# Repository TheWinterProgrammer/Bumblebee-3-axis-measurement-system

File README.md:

# Bumblebee 3-Axis Measurement System

## Overview

The **Bumblebee 3-Axis Measurement System** is a versatile, open-source, cubic positioning robot adapted for low-field MRI research. This project builds upon the design of the original [COSI Measure Robot](https://www.opensourceimaging.org/project/cosi-measure/), enhancing its mechanical and electronic capabilities. The system was redesigned during the 2023-2024 academic year as part of several bachelor theses at our institute.

### Key Features
- **Adapted Mechanical Design**  
  The robot is designed for:
  - A larger measurement volume.
  - Improved efficiency relative to the robot's size.

- **Simplified Electronics**  
  Replacing the BeagleBone Black and embedded Linux system, the new design features:
  - An **Arduino MEGA** as the central microcontroller for motor control, limit switch evaluation, and serial communication.
  - A **Python-based host PC script** to:
    - Control mapping.
    - Communicate positions to the robot.
    - Interface with the Hall sensor.

- **Sensor Integration**  
  The current setup uses the **F.W. BELL Series 9900 Hall sensor** with the ZOA99-3208 3D Hall probe. The Python script processes data from this sensor via serial communication. However, the system can accommodate other sensors as needed.

---

## Publication

This work was presented and published as a conference paper:  
**Samlow J, Maltsev S [TheWinterProgrammer](https://github.com/TheWinterProgrammer), Buckenmaier K, Scheffler K, Povolni P [ppolGTMonster](https://github.com/ppolGTMonster) (2024). Easy Rebuildable Cubic 3-Axis Positioning Robot Based on Open-Source Hardware: Validated via Camera-Based Motion Tracking and Initial Application in Magnetic Low Field Mapping.** *DACH-ISMRM 2024 Program & Proceedings, Tübingen, Germany*, pp. 1–2.

---

## Getting Started

There a tree major parts:

### System Components
1. **Hardware** [here](Hardware)
   - Rebuilt mechanical design for larger volume mapping.
   - Compact yet efficient cubic robot frame.

2. **Electronics** 
   - Arduino MEGA for robot control and interfacing [here](Software/Arduino/).
   - Support for various sensors through serial communication.

3. **Software** [here](Software/PythonGUI/)
   - Python script to manage mapping and communication.

### Usage
1. Set up the Arduino MEGA and connect the motors, limit switches, and Hall sensor.
2. Run the Python script on the host PC for:
   - Position control of the robot.
   - Real-time data collection from the Hall sensor.

---
## Author
   - Judith Samlov ([E-Mail](judith.samlov@tuebingen.mpg.de)), (Hardware and Software) 
   - Pavel Povolni ([E-Mail](pavel.povolni@tuebingen.mpg.de), [Github](https://github.com/ppolGTMonster)), (Hardware and Software)
   - Sergej Maltsev ([E-Mail](sergej.maltsev@tuebingen.mpg.de), [Github](https://github.com/TheWinterProgrammer)), (Software Python GUI)

### Contact
For further inquiries or contributions, feel free to reach out through the repository.

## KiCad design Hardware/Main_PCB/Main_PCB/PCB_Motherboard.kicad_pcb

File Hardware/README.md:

# Hardware

## Assembly Robot

The assembly of the robot, including all CAD design files and instructions, is thoroughly described and documented in the following resources:  
- [COSI Measure Project Page](https://www.opensourceimaging.org/project/cosi-measure/)  
- [COSI Measure GitHub Repository](https://github.com/opensourceimaging/cosi-measure/tree/master/Mechanical%20System)  

We recommend referring to these resources for detailed instructions. The hardware components for the drive and ordering details are also described there.

### Key Components for 3D Drive
We used the following parts for the 3D drive. These may be relevant if adapting the PCB, though similar drives should also work:

- **Motor**: NEMA23 60HS88, 3 pieces (no longer available)  
  Alternative: [HYBRID NEMA-23 Stepper Motor](https://www.reichelt.de/hybridschrittmotor-nema-23-1-8-4-2-a-2-52-v-act-23hs9440-26-p316758.html?&trstct=pos_6&nbc=1)  
- **Motor Driver**: ACT DM542, 3 pieces  
  Link: [Stepper Motor Driver ACT DM542](https://www.reichelt.de/schrittmotortreiber-fuer-nema-23-18-50-v-act-dm542-p237924.html?&trstct=pos_1&nbc=1)  
- **Limit Switch**: LJ12A3-4-Z/BX DC6-36V, 3 pieces  
  Link: [Inductive Sensor](https://www.roboter-bausatz.de/p/induktiver-sensor-lj12a3-4-z-bx-dc6-36v?number=RBS11420)  
- **Power Source**: 36V, 9.75A (350W)  
  Link: [36V Power Supply](https://www.reichelt.de/schaltnetzteil-geschlossen-351-w-36-v-9-75-a-mw-uhp-350-36-p256082.html?&trstct=pol_6&nbc=1)  

---

## Assembly PCB

### General

For this version of COSI Measure, we used an **Arduino Mega** as the central microcontroller (µC).  

While assembling, some errors in the V1.0 PCB design were identified and corrected in version V2.0, which is made available here.  

This design uses a two-part concept:  
1. **Main PCB**  
2. **Optional Remote Control**  
   - The remote control can manually adjust the Hall sensor's position. Although the remote control functionality was disabled in this setup, the buttons and encoders remain available in the hardware. Manual control has been replaced by Python-based software control.

If needed, you can design your own remote control and connect it via the 26-pin SubD connector.

### Implemented Functions

- Control of 3 stepper motors via PWM signals.  
- Safety circuit with emergency stop to disconnect motor drivers' power supply.  
- I2C output, e.g., for display integration.  
- Serial communication (USB) with the host PC.  
- Other analog inputs/outputs are available and can be used e.g. for additional sensors.

### PCB Design
- Designed using **KiCad 8** (no additional packages required).  
- Comments in the schematic provide explanatory details.  
- Uses large SMD components (e.g., SMD1206 for resistors and capacitors) for easy soldering.  
- Two-layer PCB design to reduce manufacturing costs.  
- A bill of materials (BoM) is included in the accompanying Excel sheet.  

#### Note
The PCB size can be reduced by modifying component footprints and minimizing unused connectors.

### Assembly PCB
- Large component sizes simplify soldering.  
- Arduino Mega connects via pin headers for easy replacement.  
- A cutout in the PCB allows visibility of the Arduino's built-in LED when mounted.  

### Wiring Inside the Case
The PCB, power supply, and motor drivers are all housed in a single case. Wiring is straightforward with labeled connectors on the PCB. **Phoenix 3.81mm PCB connectors** were used to facilitate cable attachment.  

#### ⚠️ Important Safety Note:
<span style="color: red;">- The power supply operates at 230V AC, which is **extremely dangerous**.</span>  
<span style="color: red;">- Electrical connections between the power input and power supply are **not documented here**.</span>  
<span style="color: red;">- **Only a qualified electrician** should handle this part. Ensure the case is grounded and use an FI-protected socket.</span>

---

## Assembly Case for Electronics

### Case Design
The case is a standard **19-inch, 2 height units** enclosure. The side profiles, front and back panels, and top and bottom panels were milled using a mechanical workshop.  

For best results, the front and back panels should be milled. Alternatively, mounting holes can be created manually. Accuracy is essential for mounting the DSub connector.  

Cooling: Two 12V fans were installed but found unnecessary during operation. Drivers were mounted on the base plate with cooling fins extending outward for heat dissipation. However, this may not be required.

### CAD Files
The case design was created using **Autodesk Inventor 2022**.  
- Files are exported as STEP files for compatibility with other CAD programs.  
- Side profiles are customizable, depending on the electronics installed.  

### Front Connections
All parts for the front panel are listed in the BoM.  
- **USB**: For Arduino Mega-PC serial communication.  
- **Limit Switches**: 25-pin Sub-D (male) for connecting up to 6 limit switches.  
- **Remote Control**: 26-pin Sub-D (female).  
- **Motor Connections**: 4-pin DIN connectors (male) for X, Y, and Z-axis motors.  
- **Power LED**: Indicates power supply status.  
- **Emergency Stop**: Cuts power to motor drivers via relay.  

### Back Connections
- **230V IEC Plug**: Includes an on/off switch and main fuse (1.75A, slow-blow).  

### Wiring
Wiring is simplified by labeled PCB connectors and depends on the components installed. For questions, please contact us.

---

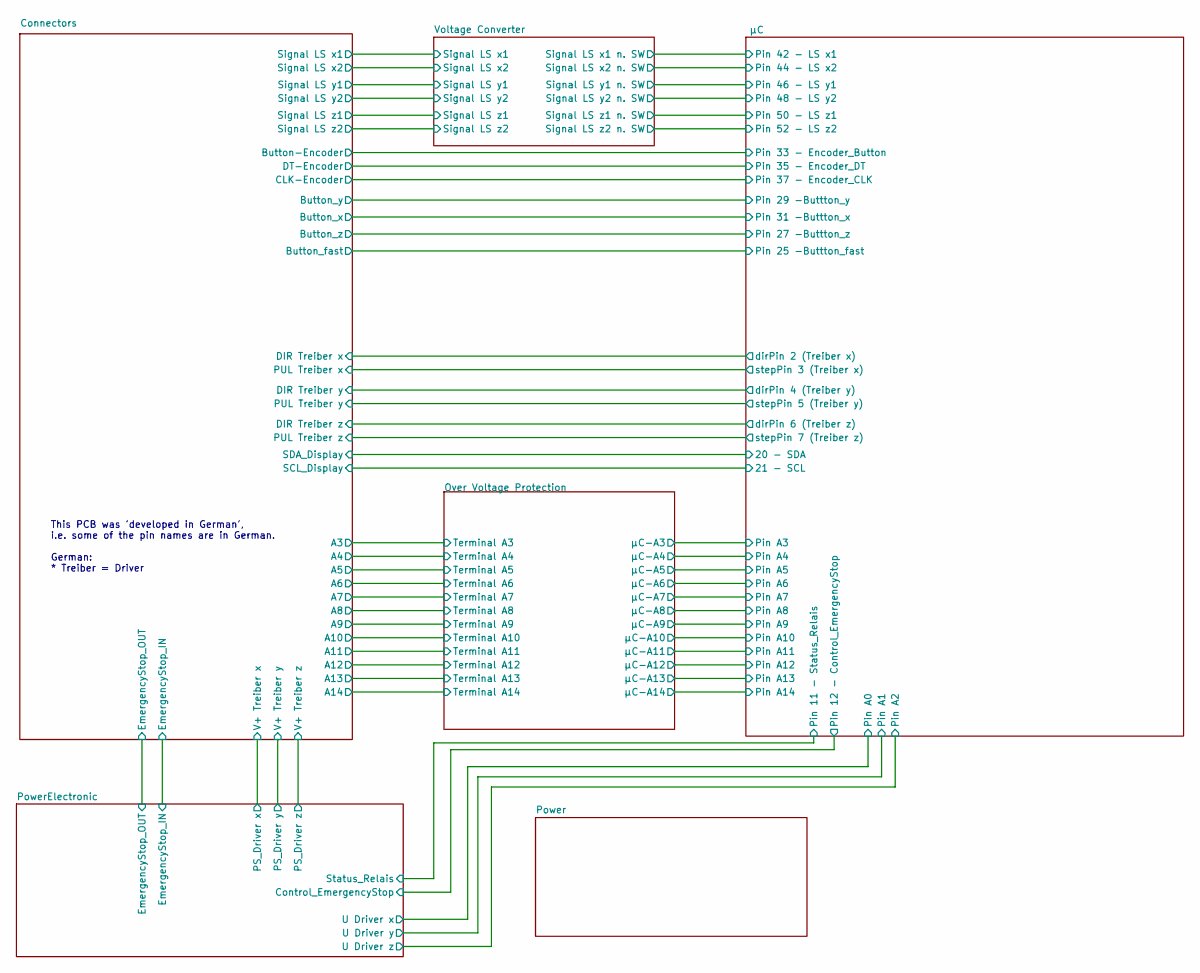
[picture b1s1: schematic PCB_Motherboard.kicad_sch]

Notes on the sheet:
This PCB was 'developed in German', i.e. some of the pin names are in German. German: * Treiber = Driver

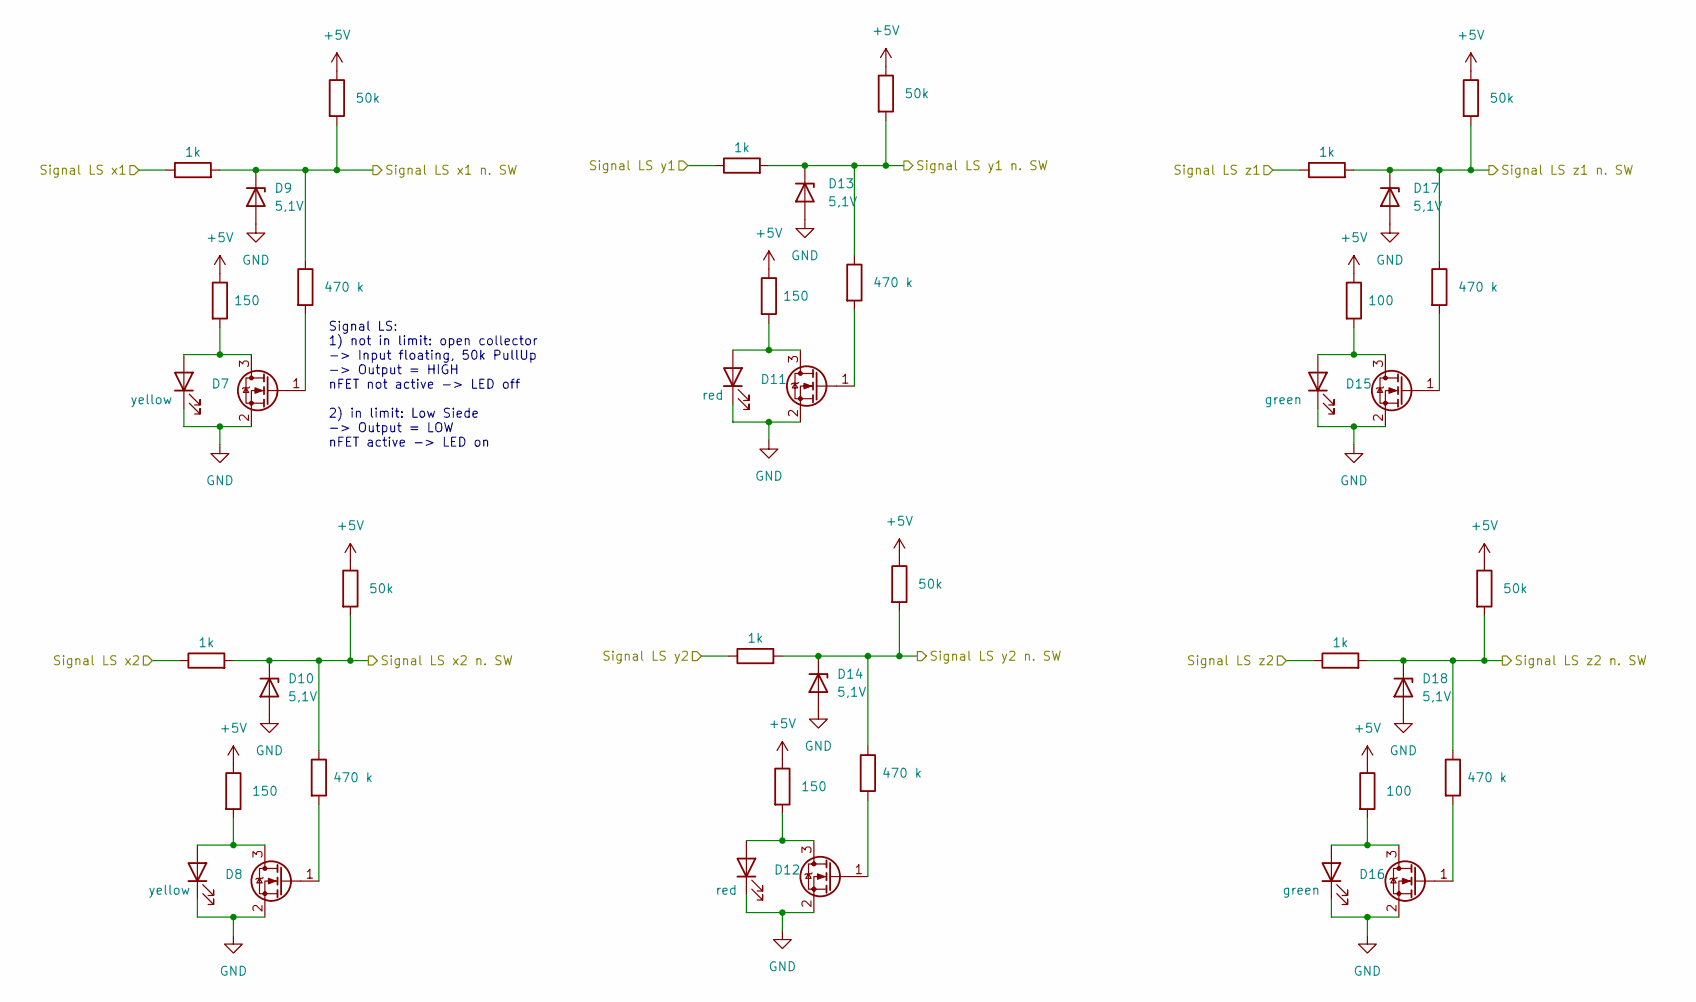
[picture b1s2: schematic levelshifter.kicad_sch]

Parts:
D7, D8: yellow; LED_0603_1608Metric_Pad1.05x0.95mm_HandSolder
D9, D10, D13, D14, D17, D18: 5,1V; D_SMA_Handsoldering
D11, D12: red; LED_0603_1608Metric_Pad1.05x0.95mm_HandSolder
D15, D16: green; LED_0603_1608Metric_Pad1.05x0.95mm_HandSolder
Q2, Q3, Q4, Q5, Q6, Q7: Q_NMOS_GDS; SOT-23
R14, R15, R22, R23, R30, R31: 1k; R_1206_3216Metric_Pad1.30x1.75mm_HandSolder
R16, R17, R24, R25: 150; R_1206_3216Metric_Pad1.30x1.75mm_HandSolder
R18, R19, R26, R27, R34, R35: 470 k; R_1206_3216Metric_Pad1.30x1.75mm_HandSolder
R20, R21, R28, R29, R36, R37: 50k; R_1206_3216Metric_Pad1.30x1.75mm_HandSolder
R32, R33: 100; R_1206_3216Metric_Pad1.30x1.75mm_HandSolder

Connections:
+5V: R16.1, R17.1, R20.1, R21.1, R24.1, R25.1, R28.1, R29.1, R32.1, R33.1, R36.1, R37.1; also elsewhere on the board
/Connectors/Signal LS x1: R14.1; also elsewhere on the board
/Connectors/Signal LS x2: R15.1; also elsewhere on the board
/Connectors/Signal LS y1: R22.1; also elsewhere on the board
/Connectors/Signal LS y2: R23.1; also elsewhere on the board
/Connectors/Signal LS z1: R30.1; also elsewhere on the board
/Connectors/Signal LS z2: R31.1; also elsewhere on the board
/Voltage Converter/Signal LS x1 n. SW: D9.1 (K), R14.2, R18.1, R20.2; also elsewhere on the board
/Voltage Converter/Signal LS x2 n. SW: D10.1 (K), R15.2, R19.1, R21.2; also elsewhere on the board
/Voltage Converter/Signal LS y1 n. SW: D13.1 (K), R22.2, R26.1, R28.2; also elsewhere on the board
/Voltage Converter/Signal LS y2 n. SW: D14.1 (K), R23.2, R27.1, R29.2; also elsewhere on the board
/Voltage Converter/Signal LS z1 n. SW: D17.1 (K), R30.2, R34.1, R36.2; also elsewhere on the board
/Voltage Converter/Signal LS z2 n. SW: D18.1 (K), R31.2, R35.1, R37.2; also elsewhere on the board
GND: D7.1 (K), D8.1 (K), D9.2 (A), D10.2 (A), D11.1 (K), D12.1 (K), D13.2 (A), D14.2 (A), D15.1 (K), D16.1 (K), D17.2 (A), D18.2 (A), Q2.2 (S), Q3.2 (S), Q4.2 (S), Q5.2 (S), Q6.2 (S), Q7.2 (S); also elsewhere on the board
unnamed: D7.2 (A), Q2.3 (D), R16.2
unnamed: D8.2 (A), Q3.3 (D), R17.2
unnamed: D11.2 (A), Q4.3 (D), R24.2
unnamed: D12.2 (A), Q5.3 (D), R25.2
unnamed: D15.2 (A), Q6.3 (D), R32.2
unnamed: D16.2 (A), Q7.3 (D), R33.2
unnamed: Q2.1 (G), R18.2
unnamed: Q3.1 (G), R19.2
unnamed: Q4.1 (G), R26.2
unnamed: Q5.1 (G), R27.2
unnamed: Q6.1 (G), R34.2
unnamed: Q7.1 (G), R35.2

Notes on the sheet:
Signal LS: 1) not in limit: open collector -> Input floating, 50k PullUp -> Output = HIGH nFET not active -> LED off 2) in limit: Low Siede -> Output = LOW nFET active -> LED on

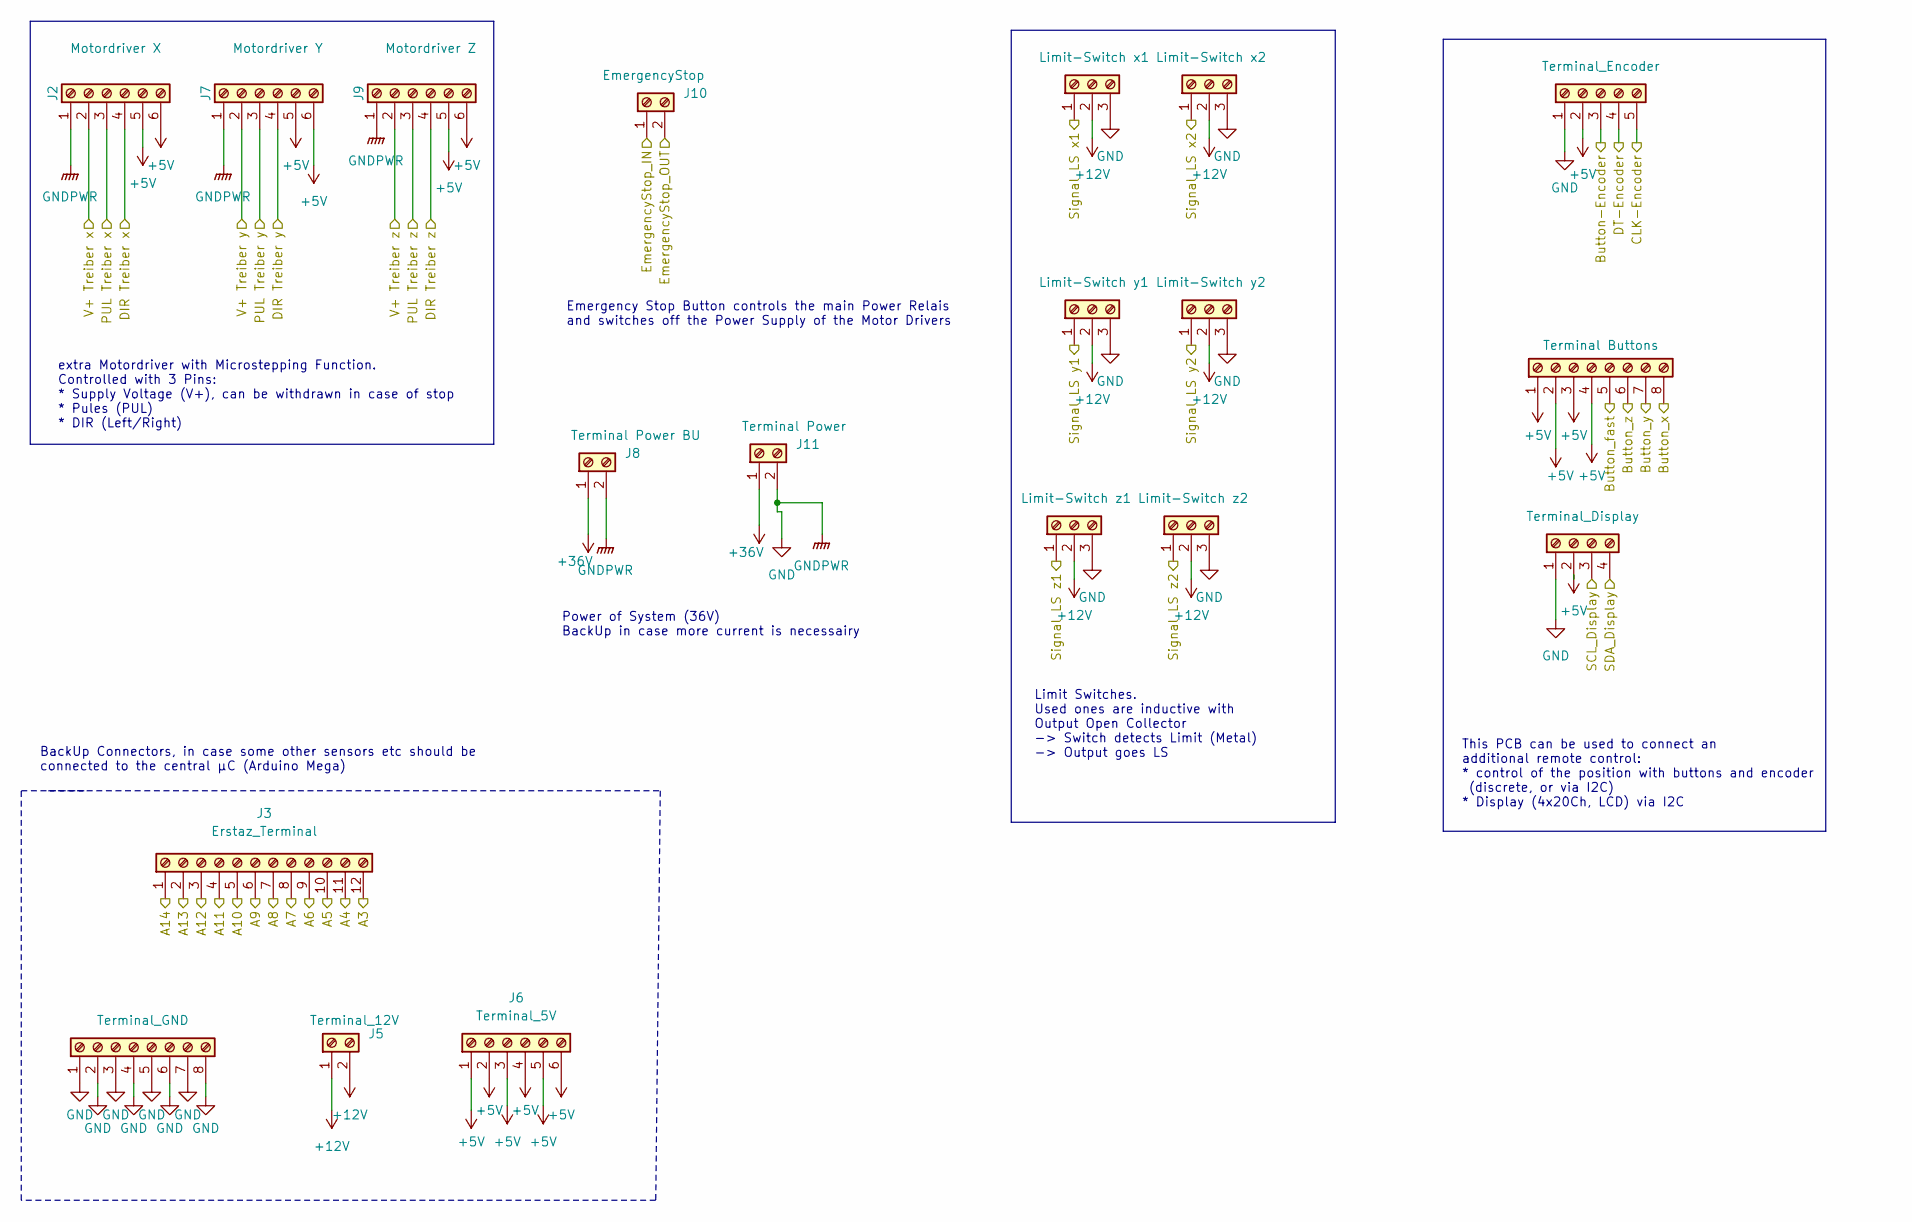
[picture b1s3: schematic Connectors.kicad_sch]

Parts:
J1: Terminal_Display; PhoenixContact_MC_1,5_4-G-3.81_1x04_P3.81mm_Horizontal
J2: Motordriver X; PhoenixContact_MC_1,5_6-G-3.81_1x06_P3.81mm_Horizontal
J3: Erstaz_Terminal; PhoenixContact_MC_1,5_12-G-3.81_1x12_P3.81mm_Horizontal
J4: Terminal_GND; PhoenixContact_MC_1,5_8-G-3.81_1x08_P3.81mm_Horizontal
J5: Terminal_12V; PhoenixContact_MC_1,5_2-G-3.81_1x02_P3.81mm_Horizontal
J6: Terminal_5V; PhoenixContact_MC_1,5_6-G-3.81_1x06_P3.81mm_Horizontal
J7: Motordriver Y; PhoenixContact_MC_1,5_6-G-3.81_1x06_P3.81mm_Horizontal
J8: Terminal Power BU; PhoenixContact_MC_1,5_2-G-3.81_1x02_P3.81mm_Horizontal
J9: Motordriver Z; PhoenixContact_MC_1,5_6-G-3.81_1x06_P3.81mm_Horizontal
J10: EmergencyStop; PhoenixContact_MC_1,5_2-G-3.81_1x02_P3.81mm_Horizontal
J11: Terminal Power; PhoenixContact_MC_1,5_2-G-3.81_1x02_P3.81mm_Horizontal
J12: Limit-Switch z1; PhoenixContact_MC_1,5_3-G-3.81_1x03_P3.81mm_Horizontal
J13: Limit-Switch x1; PhoenixContact_MC_1,5_3-G-3.81_1x03_P3.81mm_Horizontal
J14: Limit-Switch y1; PhoenixContact_MC_1,5_3-G-3.81_1x03_P3.81mm_Horizontal
J15: Limit-Switch z2; PhoenixContact_MC_1,5_3-G-3.81_1x03_P3.81mm_Horizontal
J16: Limit-Switch x2; PhoenixContact_MC_1,5_3-G-3.81_1x03_P3.81mm_Horizontal
J17: Limit-Switch y2; PhoenixContact_MC_1,5_3-G-3.81_1x03_P3.81mm_Horizontal
J18: Terminal Buttons; PhoenixContact_MC_1,5_8-G-3.81_1x08_P3.81mm_Horizontal
J19: Terminal_Encoder; PhoenixContact_MC_1,5_5-G-3.81_1x05_P3.81mm_Horizontal

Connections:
+5V: J1.2, J2.5, J2.6, J6.1, J6.2, J6.3, J6.4, J6.5, J6.6, J7.5, J7.6, J9.5, J9.6, J18.1, J18.2, J18.3, J18.4, J19.2; also elsewhere on the board
+12V: J5.1, J5.2, J12.2, J13.2, J14.2, J15.2, J16.2, J17.2; also elsewhere on the board
+36V: J8.1, J11.1; also elsewhere on the board
/Connectors/A3: J3.12; also elsewhere on the board
/Connectors/A4: J3.11; also elsewhere on the board
/Connectors/A5: J3.10; also elsewhere on the board
/Connectors/A6: J3.9; also elsewhere on the board
/Connectors/A7: J3.8; also elsewhere on the board
/Connectors/A8: J3.7; also elsewhere on the board
/Connectors/A9: J3.6; also elsewhere on the board
/Connectors/A10: J3.5; also elsewhere on the board
/Connectors/A11: J3.4; also elsewhere on the board
/Connectors/A12: J3.3; also elsewhere on the board
/Connectors/A13: J3.2; also elsewhere on the board
/Connectors/A14: J3.1; also elsewhere on the board
/Connectors/Button-Encoder: J19.3; also elsewhere on the board
/Connectors/Button_fast: J18.5; also elsewhere on the board
/Connectors/Button_x: J18.8; also elsewhere on the board
/Connectors/Button_y: J18.7; also elsewhere on the board
/Connectors/Button_z: J18.6; also elsewhere on the board
/Connectors/CLK-Encoder: J19.5; also elsewhere on the board
/Connectors/DIR Treiber x: J2.4; also elsewhere on the board
/Connectors/DIR Treiber y: J7.4; also elsewhere on the board
/Connectors/DIR Treiber z: J9.4; also elsewhere on the board
/Connectors/DT-Encoder: J19.4; also elsewhere on the board
/Connectors/EmergencyStop_IN: J10.1; also elsewhere on the board
/Connectors/EmergencyStop_OUT: J10.2; also elsewhere on the board
/Connectors/PUL Treiber x: J2.3; also elsewhere on the board
/Connectors/PUL Treiber y: J7.3; also elsewhere on the board
/Connectors/PUL Treiber z: J9.3; also elsewhere on the board
/Connectors/SCL_Display: J1.3; also elsewhere on the board
/Connectors/SDA_Display: J1.4; also elsewhere on the board
/Connectors/Signal LS x1: J13.1; also elsewhere on the board
/Connectors/Signal LS x2: J16.1; also elsewhere on the board
/Connectors/Signal LS y1: J14.1; also elsewhere on the board
/Connectors/Signal LS y2: J17.1; also elsewhere on the board
/Connectors/Signal LS z1: J12.1; also elsewhere on the board
/Connectors/Signal LS z2: J15.1; also elsewhere on the board
/Connectors/V+ Treiber x: J2.2; also elsewhere on the board
/Connectors/V+ Treiber y: J7.2; also elsewhere on the board
/Connectors/V+ Treiber z: J9.2; also elsewhere on the board
GND: J1.1, J2.1, J4.1, J4.2, J4.3, J4.4, J4.5, J4.6, J4.7, J4.8, J7.1, J8.2, J9.1, J11.2, J12.3, J13.3, J14.3, J15.3, J16.3, J17.3, J19.1; also elsewhere on the board

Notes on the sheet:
Power of System (36V) BackUp in case more current is necessairy
Emergency Stop Button controls the main Power Relais and switches off the Power Supply of the Motor Drivers
This PCB can be used to connect an additional remote control: * control of the position with buttons and encoder (discrete, or via I2C) * Display (4x20Ch, LCD) via I2C
extra Motordriver with Microstepping Function. Controlled with 3 Pins: * Supply Voltage (V+), can be withdrawn in case of stop * Pules (PUL) * DIR (Left/Right)
Limit Switches. Used ones are inductive with Output Open Collector -> Switch detects Limit (Metal) -> Output goes LS
BackUp Connectors, in case some other sensors etc should be connected to the central µC (Arduino Mega)

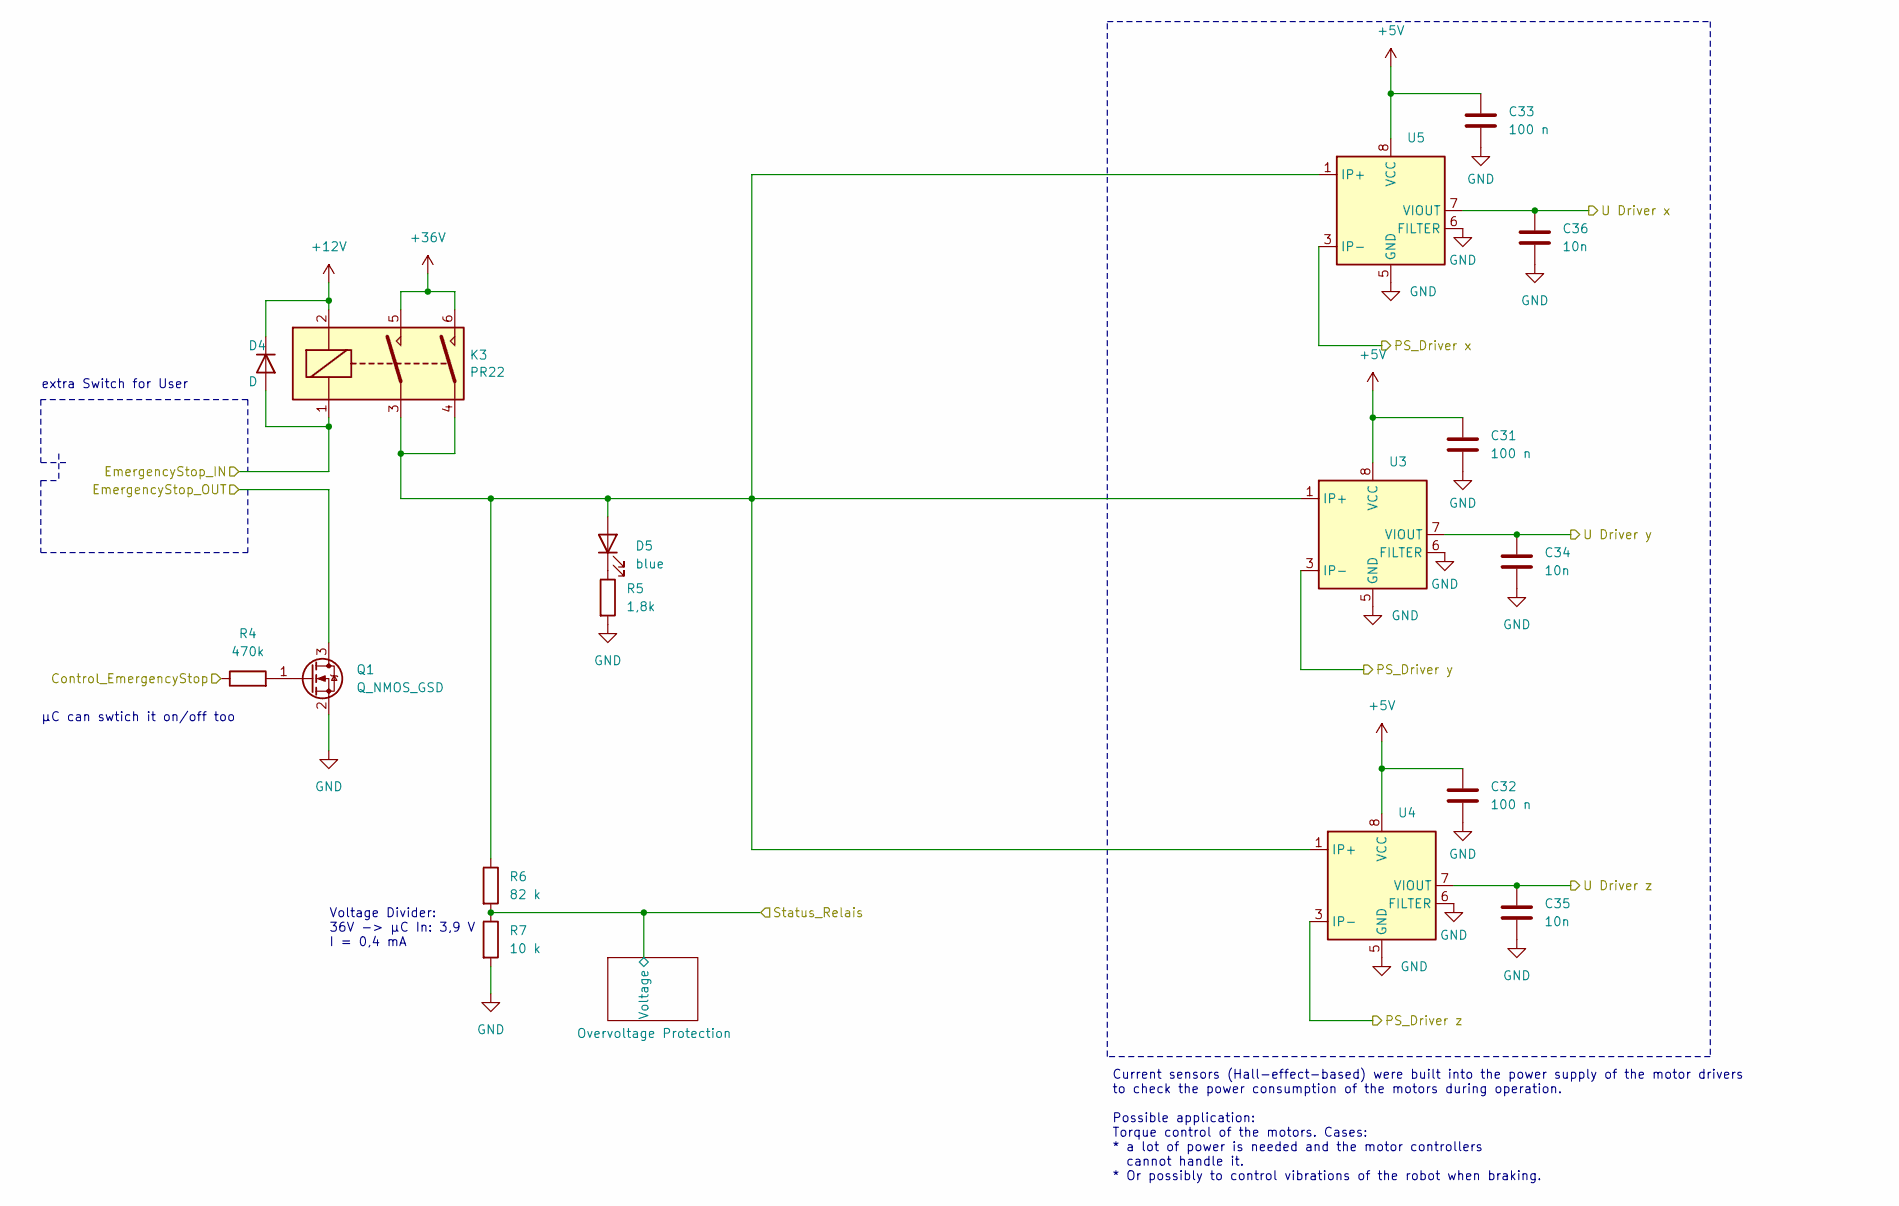
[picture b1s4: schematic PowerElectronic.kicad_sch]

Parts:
C31, C32, C33: 100 n; C_1206_3216Metric_Pad1.33x1.80mm_HandSolder
C34, C35, C36: 10n; C_1206_3216Metric_Pad1.33x1.80mm_HandSolder
D4: D; D_1206_3216Metric_Pad1.42x1.75mm_HandSolder
D5: blue; LED_0603_1608Metric_Pad1.05x0.95mm_HandSolder
K3: PR22; Relay_PR22
Q1: Q_NMOS_GSD; SOT-23
R4: 470k; R_1206_3216Metric_Pad1.30x1.75mm_HandSolder
R5: 1,8k; R_1206_3216Metric_Pad1.30x1.75mm_HandSolder
R6: 82 k; R_1206_3216Metric_Pad1.30x1.75mm_HandSolder
R7: 10 k; R_1206_3216Metric_Pad1.30x1.75mm_HandSolder
U3, U4, U5: SOIC-8_3.9x4.9mm_P1.27mm

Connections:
+5V: C31.1, C32.1, C33.1, U3.8 (VCC), U4.8 (VCC), U5.8 (VCC); also elsewhere on the board
+12V: D4.1 (K), K3.2; also elsewhere on the board
+36V: K3.5, K3.6; also elsewhere on the board
/Connectors/EmergencyStop_IN: D4.2 (A), K3.1; also elsewhere on the board
/Connectors/EmergencyStop_OUT: Q1.3 (D); also elsewhere on the board
/Connectors/V+ Treiber x: U5.3 (IP-), U5.4 (IP-); also elsewhere on the board
/Connectors/V+ Treiber y: U3.3 (IP-), U3.4 (IP-); also elsewhere on the board
/Connectors/V+ Treiber z: U4.3 (IP-), U4.4 (IP-); also elsewhere on the board
/PowerElectronic/Control_EmergencyStop: R4.1; also elsewhere on the board
/PowerElectronic/Status_Relais: R6.2, R7.1; also elsewhere on the board
/PowerElectronic/U Driver x: C36.1, U5.7 (VIOUT); also elsewhere on the board
/PowerElectronic/U Driver y: C34.1, U3.7 (VIOUT); also elsewhere on the board
/PowerElectronic/U Driver z: C35.1, U4.7 (VIOUT); also elsewhere on the board
GND: C31.2, C32.2, C33.2, C34.2, C35.2, C36.2, Q1.2 (S), R5.2, R7.2, U3.5 (GND), U3.6 (FILTER), U4.5 (GND), U4.6 (FILTER), U5.5 (GND), U5.6 (FILTER); also elsewhere on the board
unnamed: D5.2 (A), K3.3, K3.4, R6.1, U3.1 (IP+), U3.2 (IP+), U4.1 (IP+), U4.2 (IP+), U5.1 (IP+), U5.2 (IP+)
unnamed: D5.1 (K), R5.1
unnamed: Q1.1 (G), R4.2

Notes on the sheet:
Current sensors (Hall-effect-based) were built into the power supply of the motor drivers to check the power consumption of the motors during operation. Possible application: Torque control of the motors. Cases: * a lot of power is needed and the motor controllers cannot handle it. * Or possibly to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
Voltage Divider: 36V -> µC In: 3,9 V I = 0,4 mA
µC can swtich it on/off too
extra Switch for User

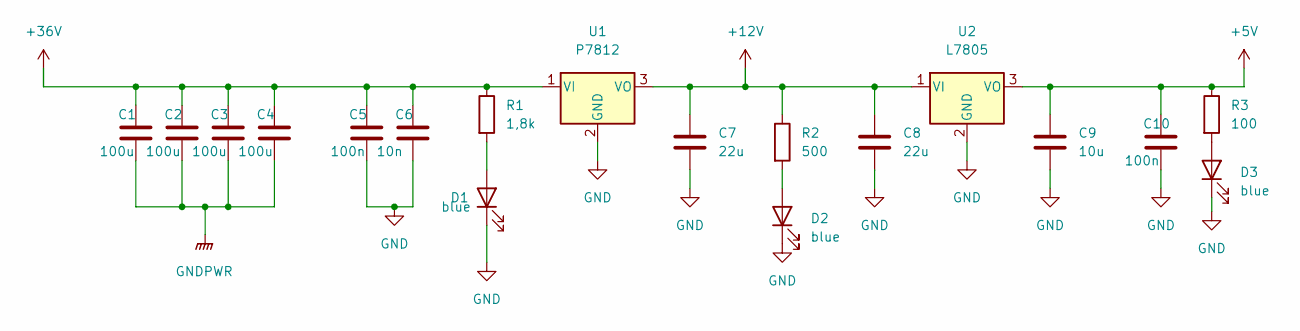
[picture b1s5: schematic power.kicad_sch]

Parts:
C1, C2, C3, C4: 100u; CP_Elec_8x6.2
C5, C10: 100n; C_1206_3216Metric_Pad1.33x1.80mm_HandSolder
C6: 10n; C_1206_3216Metric_Pad1.33x1.80mm_HandSolder
C7, C8: 22u; C_1206_3216Metric_Pad1.33x1.80mm_HandSolder
C9: 10u; C_1206_3216Metric_Pad1.33x1.80mm_HandSolder
D1, D2, D3: blue; LED_0603_1608Metric_Pad1.05x0.95mm_HandSolder
R1: 1,8k; R_1206_3216Metric_Pad1.30x1.75mm_HandSolder
R2: 500; R_1206_3216Metric_Pad1.30x1.75mm_HandSolder
R3: 100; R_1206_3216Metric_Pad1.30x1.75mm_HandSolder
U1: P7812
U2: L7805; P7812

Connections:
+5V: C9.1, C10.1, R3.1, U2.3 (VO); also elsewhere on the board
+12V: C7.1, C8.1, R2.1, U1.3 (VO), U2.1 (VI); also elsewhere on the board
+36V: C1.1, C2.1, C3.1, C4.1, C5.1, C6.1, R1.1, U1.1 (VI); also elsewhere on the board
GND: C1.2, C2.2, C3.2, C4.2, C5.2, C6.2, C7.2, C8.2, C9.2, C10.2, D1.1 (K), D2.1 (K), D3.1 (K), U1.2 (GND), U2.2 (GND); also elsewhere on the board
unnamed: D1.2 (A), R1.2
unnamed: D2.2 (A), R2.2
unnamed: D3.2 (A), R3.2

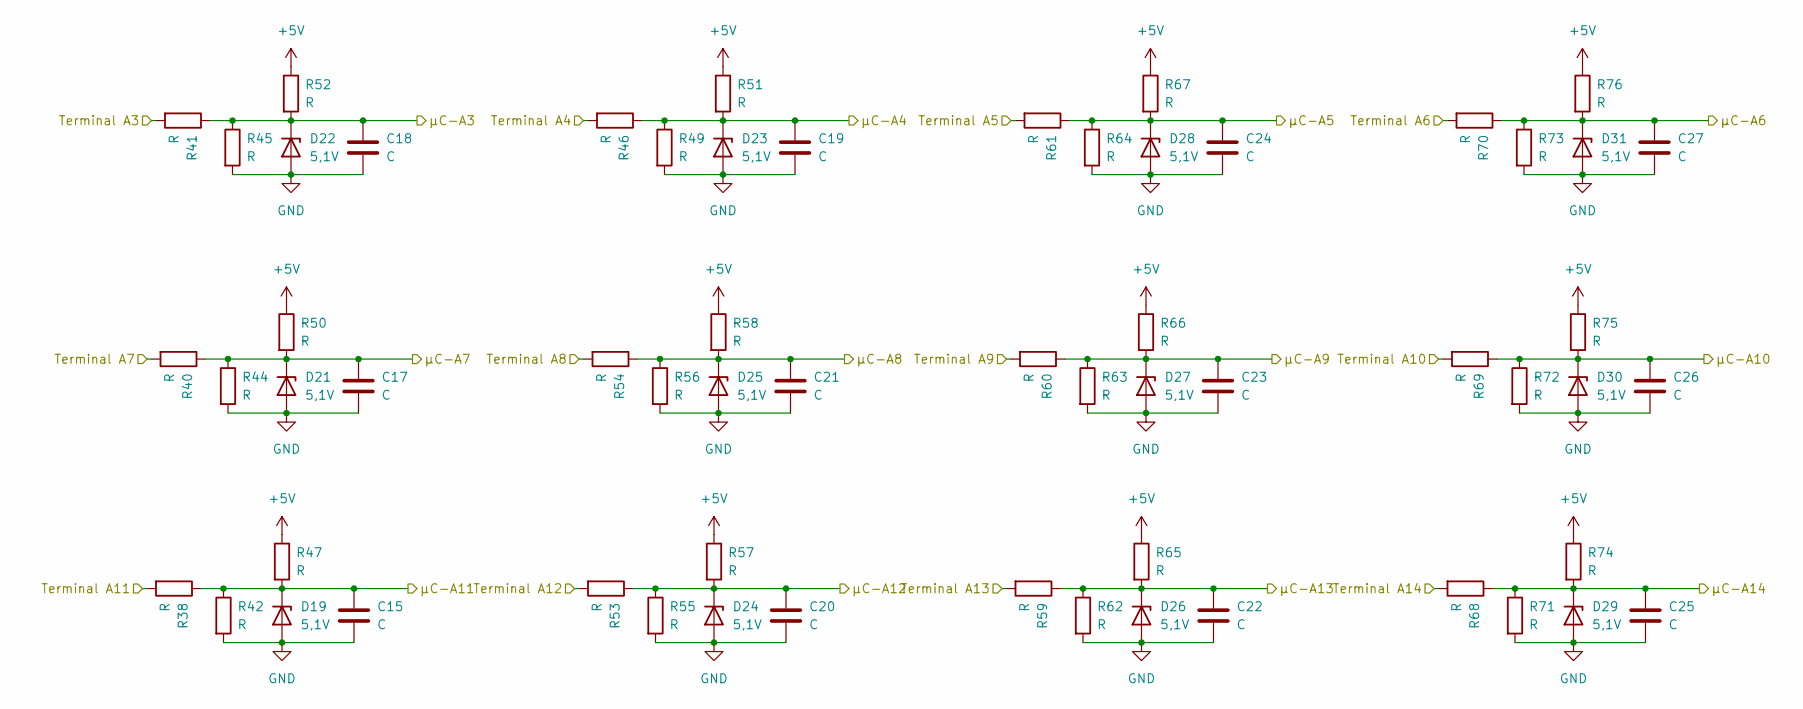
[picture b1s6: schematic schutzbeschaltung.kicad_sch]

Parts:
C15, C17, C18, C19, C20, C21, C22, C23, C24, C25, C26, C27: C; C_1206_3216Metric_Pad1.33x1.80mm_HandSolder
D19, D21, D22, D23, D24, D25, D26, D27, D28, D29, D30, D31: 5,1V; D_SMA_Handsoldering
R38, R40, R41, R42, R44, R45, R46, R47, R49, R50, R51, R52, R53, R54, R55, R56, R57, R58, R59, R60, R61, R62, R63, R64, R65, R66, R67, R68, R69, R70, R71, R72, R73, R74, R75, R76: R; R_1206_3216Metric_Pad1.30x1.75mm_HandSolder

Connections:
+5V: R47.1, R50.1, R51.1, R52.1, R57.1, R58.1, R65.1, R66.1, R67.1, R74.1, R75.1, R76.1; also elsewhere on the board
/Connectors/A3: R41.2; also elsewhere on the board
/Connectors/A4: R46.2; also elsewhere on the board
/Connectors/A5: R61.2; also elsewhere on the board
/Connectors/A6: R70.2; also elsewhere on the board
/Connectors/A7: R40.2; also elsewhere on the board
/Connectors/A8: R54.2; also elsewhere on the board
/Connectors/A9: R60.2; also elsewhere on the board
/Connectors/A10: R69.2; also elsewhere on the board
/Connectors/A11: R38.2; also elsewhere on the board
/Connectors/A12: R53.2; also elsewhere on the board
/Connectors/A13: R59.2; also elsewhere on the board
/Connectors/A14: R68.2; also elsewhere on the board
/Over Voltage Protection/µC-A3: C18.1, D22.1 (K), R41.1, R45.1, R52.2; also elsewhere on the board
/Over Voltage Protection/µC-A4: C19.1, D23.1 (K), R46.1, R49.1, R51.2; also elsewhere on the board
/Over Voltage Protection/µC-A5: C24.1, D28.1 (K), R61.1, R64.1, R67.2; also elsewhere on the board
/Over Voltage Protection/µC-A6: C27.1, D31.1 (K), R70.1, R73.1, R76.2; also elsewhere on the board
/Over Voltage Protection/µC-A7: C17.1, D21.1 (K), R40.1, R44.1, R50.2; also elsewhere on the board
/Over Voltage Protection/µC-A8: C21.1, D25.1 (K), R54.1, R56.1, R58.2; also elsewhere on the board
/Over Voltage Protection/µC-A9: C23.1, D27.1 (K), R60.1, R63.1, R66.2; also elsewhere on the board
/Over Voltage Protection/µC-A10: C26.1, D30.1 (K), R69.1, R72.1, R75.2; also elsewhere on the board
/Over Voltage Protection/µC-A11: C15.1, D19.1 (K), R38.1, R42.1, R47.2; also elsewhere on the board
/Over Voltage Protection/µC-A12: C20.1, D24.1 (K), R53.1, R55.1, R57.2; also elsewhere on the board
/Over Voltage Protection/µC-A13: C22.1, D26.1 (K), R59.1, R62.1, R65.2; also elsewhere on the board
/Over Voltage Protection/µC-A14: C25.1, D29.1 (K), R68.1, R71.1, R74.2; also elsewhere on the board
GND: C15.2, C17.2, C18.2, C19.2, C20.2, C21.2, C22.2, C23.2, C24.2, C25.2, C26.2, C27.2, D19.2 (A), D21.2 (A), D22.2 (A), D23.2 (A), D24.2 (A), D25.2 (A), D26.2 (A), D27.2 (A), D28.2 (A), D29.2 (A), D30.2 (A), D31.2 (A), R42.2, R44.2, R45.2, R49.2, R55.2, R56.2, R62.2, R63.2, R64.2, R71.2, R72.2, R73.2; also elsewhere on the board
